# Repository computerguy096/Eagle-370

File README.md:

# Eagle-370
A clone of the original Powerleap PL-iP3/T adapter done in KiCad.

Keep in mind this is not finished, use it at your own risk.

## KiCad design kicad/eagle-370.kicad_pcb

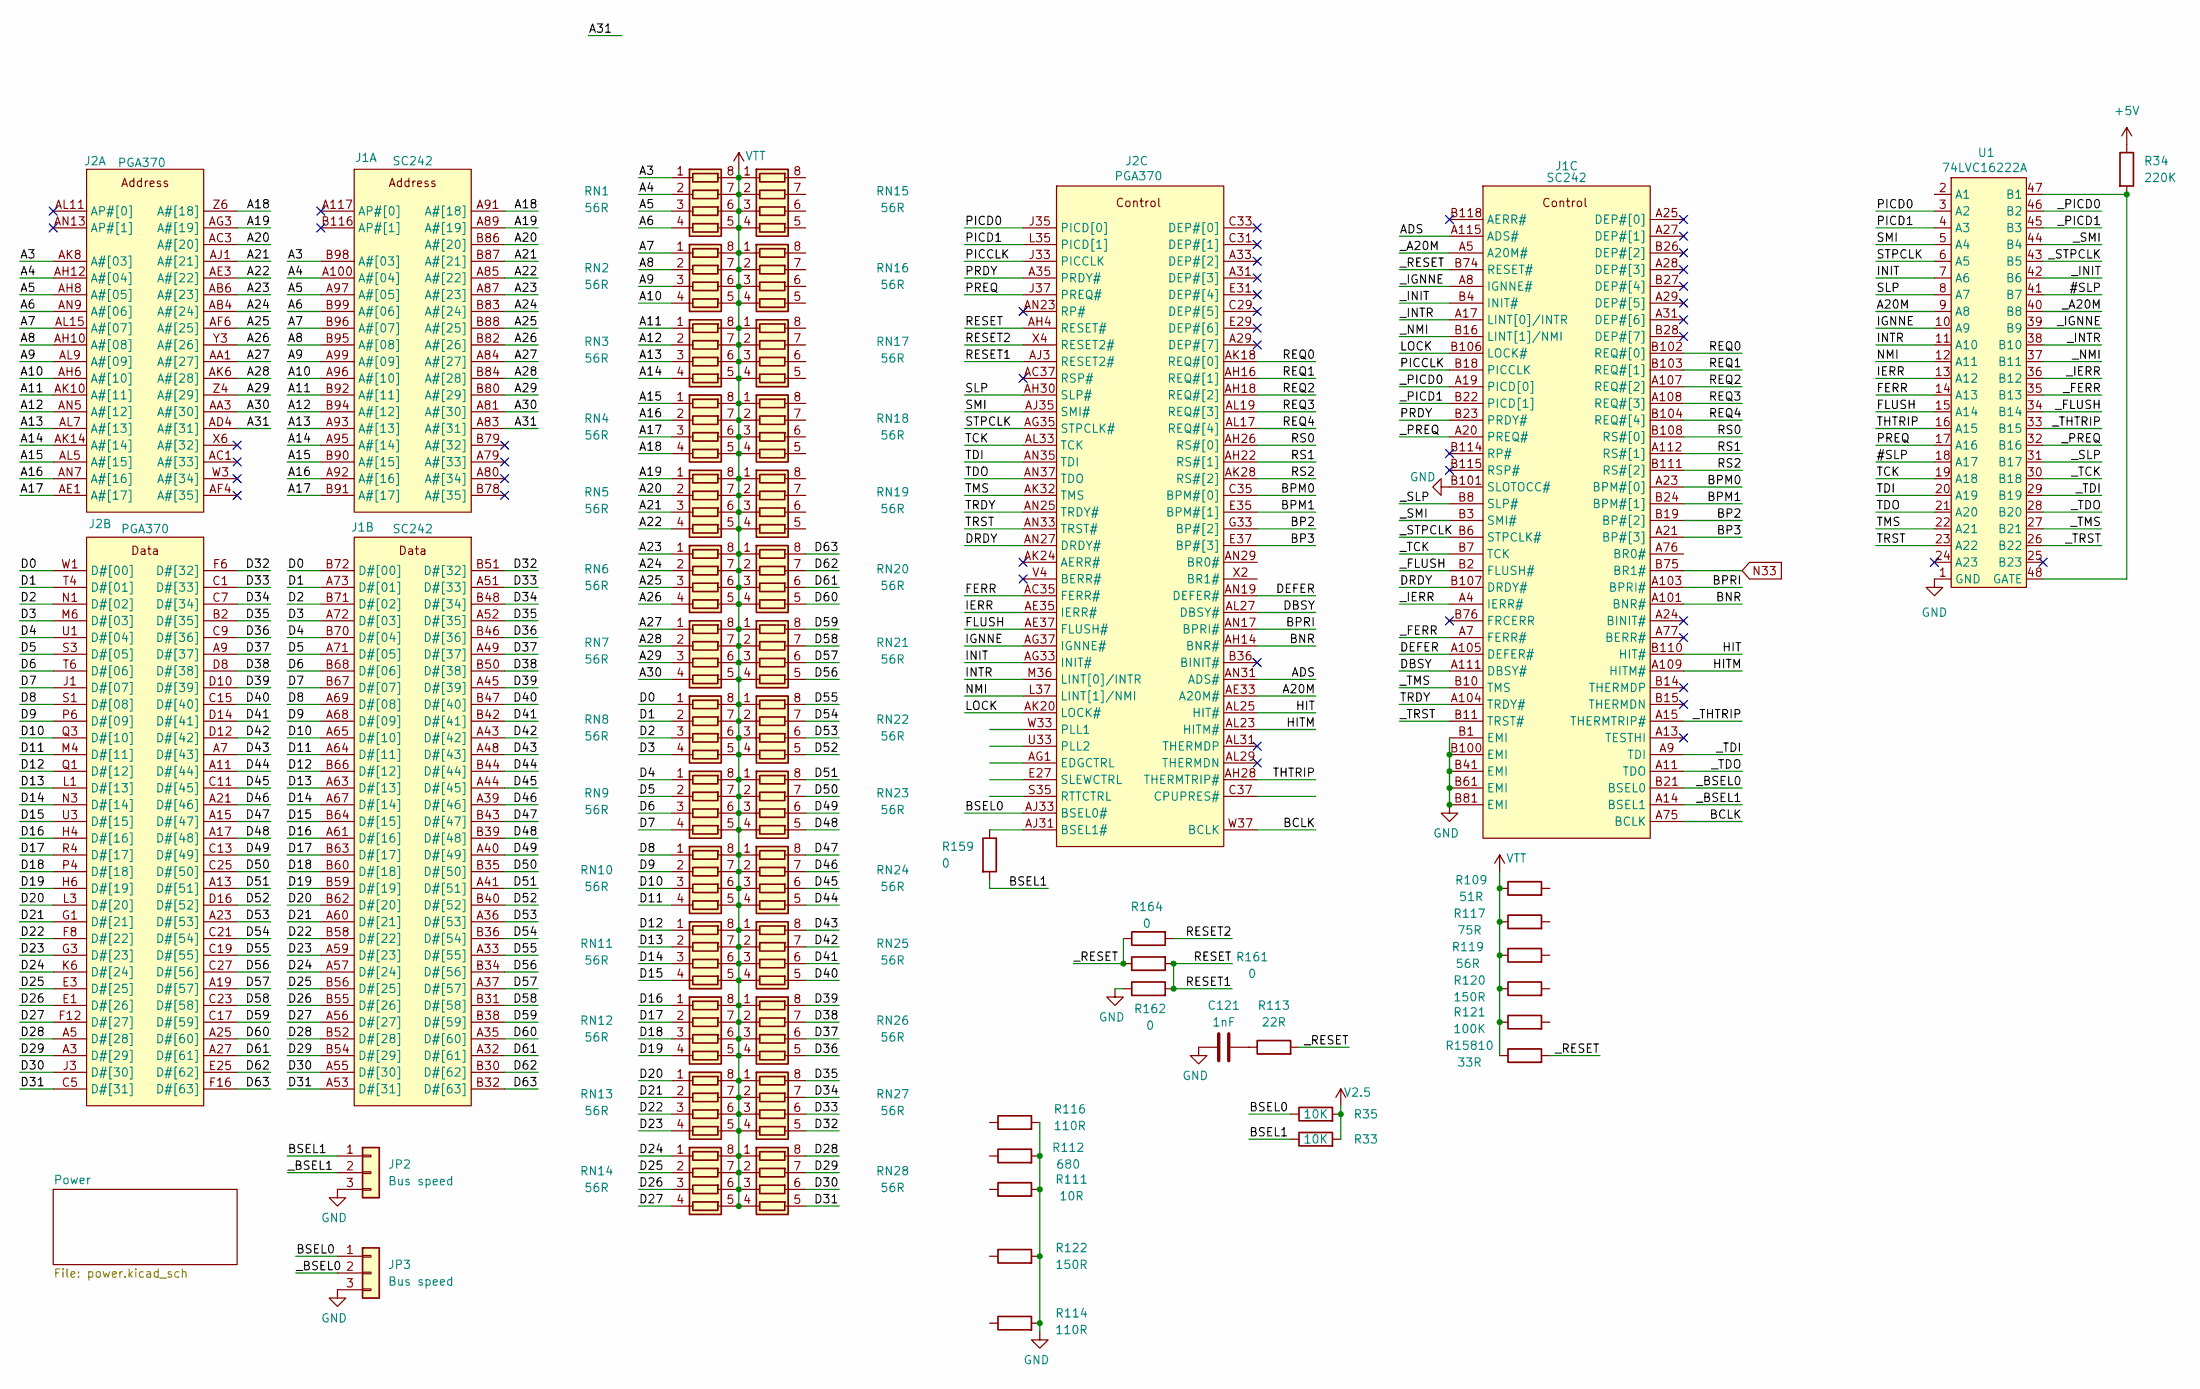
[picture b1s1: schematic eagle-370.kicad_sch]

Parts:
C121: 1nF; C_0805_2012Metric_Pad1.18x1.45mm_HandSolder
J1: SC242; Slot 1
J2: PGA370
JP2, JP3: Bus speed
R33, R35: 10K; R_0805_2012Metric_Pad1.20x1.40mm_HandSolder
R34: 220K; R_0805_2012Metric_Pad1.20x1.40mm_HandSolder
R109: 51R; R_0805_2012Metric_Pad1.20x1.40mm_HandSolder
R111: 10R; R_0805_2012Metric_Pad1.20x1.40mm_HandSolder
R112: 680; R_0805_2012Metric_Pad1.20x1.40mm_HandSolder
R113: 22R; R_0805_2012Metric_Pad1.20x1.40mm_HandSolder
R114, R116: 110R; R_0805_2012Metric_Pad1.20x1.40mm_HandSolder
R117: 75R; R_0805_2012Metric_Pad1.20x1.40mm_HandSolder
R119: 56R; R_0805_2012Metric_Pad1.20x1.40mm_HandSolder
R120, R122: 150R; R_0805_2012Metric_Pad1.20x1.40mm_HandSolder
R121: 100K; R_0805_2012Metric_Pad1.20x1.40mm_HandSolder
R159, R161, R162, R164: 0; R_0805_2012Metric_Pad1.20x1.40mm_HandSolder
R15810: 33R; R_0805_2012Metric_Pad1.20x1.40mm_HandSolder
RN1, RN2, RN3, RN4, RN5, RN6, RN7, RN8, RN9, RN10, RN11, RN12, RN13, RN14, RN15, RN16, RN17, RN18, RN19, RN20, RN21, RN22, RN23, RN24, RN25, RN26, RN27, RN28: 56R; R_Array_Convex_4x0612
U1: 74LVC16222A; SSOP-48_7.5x15.9mm_P0.635mm long pads

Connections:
+5V: R34.1
/#SLP: U1.18 (A17), U1.41 (B7)
/A3: J1.B98 (A#[03]), J2.AK8 (A#[03]), RN1.1 (R1.1)
/A4: J1.A100 (A#[04]), J2.AH12 (A#[04]), RN1.2 (R2.1)
/A5: J1.A97 (A#[05]), J2.AH8 (A#[05]), RN1.3 (R3.1)
/A6: J1.B99 (A#[06]), J2.AN9 (A#[06]), RN1.4 (R4.1)
/A7: J1.B96 (A#[07]), J2.AL15 (A#[07]), RN2.1 (R1.1)
/A8: J1.B95 (A#[08]), J2.AH10 (A#[08]), RN2.2 (R2.1)
/A9: J1.A99 (A#[09]), J2.AL9 (A#[09]), RN2.3 (R3.1)
/A10: J1.A96 (A#[10]), J2.AH6 (A#[10]), RN2.4 (R4.1)
/A11: J1.B92 (A#[11]), J2.AK10 (A#[11]), RN3.1 (R1.1)
/A12: J1.B94 (A#[12]), J2.AN5 (A#[12]), RN3.2 (R2.1)
/A13: J1.A93 (A#[13]), J2.AL7 (A#[13]), RN3.3 (R3.1)
/A14: J1.A95 (A#[14]), J2.AK14 (A#[14]), RN3.4 (R4.1)
/A15: J1.B90 (A#[15]), J2.AL5 (A#[15]), RN4.1 (R1.1)
/A16: J1.A92 (A#[16]), J2.AN7 (A#[16]), RN4.2 (R2.1)
/A17: J1.B91 (A#[17]), J2.AE1 (A#[17]), RN4.3 (R3.1)
/A18: J1.A91 (A#[18]), J2.Z6 (A#[18]), RN4.4 (R4.1)
/A19: J1.A89 (A#[19]), J2.AG3 (A#[19]), RN5.1 (R1.1)
/A20: J1.B86 (A#[20]), J2.AC3 (A#[20]), RN5.2 (R2.1)
/A20M: J2.AE33 (A20M#), U1.9 (A8)
/A21: J1.B87 (A#[21]), J2.AJ1 (A#[21]), RN5.3 (R3.1)
/A22: J1.A85 (A#[22]), J2.AE3 (A#[22]), RN5.4 (R4.1)
/A23: J1.A87 (A#[23]), J2.AB6 (A#[23]), RN6.1 (R1.1)
/A24: J1.B83 (A#[24]), J2.AB4 (A#[24]), RN6.2 (R2.1)
/A25: J1.B88 (A#[25]), J2.AF6 (A#[25]), RN6.3 (R3.1)
/A26: J1.B82 (A#[26]), J2.Y3 (A#[26]), RN6.4 (R4.1)
/A27: J1.A84 (A#[27]), J2.AA1 (A#[27]), RN7.1 (R1.1)
/A28: J1.B84 (A#[28]), J2.AK6 (A#[28]), RN7.2 (R2.1)
/A29: J1.B80 (A#[29]), J2.Z4 (A#[29]), RN7.3 (R3.1)
/A30: J1.A81 (A#[30]), J2.AA3 (A#[30]), RN7.4 (R4.1)
/A31: J1.A83 (A#[31]), J2.AD4 (A#[31])
/ADS: J1.A115 (ADS#), J2.AN31 (ADS#)
/BCLK: J1.A75 (BCLK), J2.W37 (BCLK)
/BNR: J1.A101 (BNR#), J2.AH14 (BNR#)
/BP2: J1.B19 (BP#[2]), J2.G33 (BP#[2])
/BP3: J1.A21 (BP#[3]), J2.E37 (BP#[3])
/BPM0: J1.A23 (BPM#[0]), J2.C35 (BPM#[0])
/BPM1: J1.B24 (BPM#[1]), J2.E35 (BPM#[1])
/BPRI: J1.A103 (BPRI#), J2.AN17 (BPRI#)
/BSEL0: J2.AJ33 (BSEL0#), JP3.1, R35.1
/BSEL1: JP2.1, R33.1, R159.2
/D0: J1.B72 (D#[00]), J2.W1 (D#[00]), RN8.1 (R1.1)
/D1: J1.A73 (D#[01]), J2.T4 (D#[01]), RN8.2 (R2.1)
/D2: J1.B71 (D#[02]), J2.N1 (D#[02]), RN8.3 (R3.1)
/D3: J1.A72 (D#[03]), J2.M6 (D#[03]), RN8.4 (R4.1)
/D4: J1.B70 (D#[04]), J2.U1 (D#[04]), RN9.1 (R1.1)
/D5: J1.A71 (D#[05]), J2.S3 (D#[05]), RN9.2 (R2.1)
/D6: J1.B68 (D#[06]), J2.T6 (D#[06]), RN9.3 (R3.1)
/D7: J1.B67 (D#[07]), J2.J1 (D#[07]), RN9.4 (R4.1)
/D8: J1.A69 (D#[08]), J2.S1 (D#[08]), RN10.1 (R1.1)
/D9: J1.A68 (D#[09]), J2.P6 (D#[09]), RN10.2 (R2.1)
/D10: J1.A65 (D#[10]), J2.Q3 (D#[10]), RN10.3 (R3.1)
/D11: J1.A64 (D#[11]), J2.M4 (D#[11]), RN10.4 (R4.1)
/D12: J1.B66 (D#[12]), J2.Q1 (D#[12]), RN11.1 (R1.1)
/D13: J1.A63 (D#[13]), J2.L1 (D#[13]), RN11.2 (R2.1)
/D14: J1.A67 (D#[14]), J2.N3 (D#[14]), RN11.3 (R3.1)
/D15: J1.B64 (D#[15]), J2.U3 (D#[15]), RN11.4 (R4.1)
/D16: J1.A61 (D#[16]), J2.H4 (D#[16]), RN12.1 (R1.1)
/D17: J1.B63 (D#[17]), J2.R4 (D#[17]), RN12.2 (R2.1)
/D18: J1.B60 (D#[18]), J2.P4 (D#[18]), RN12.3 (R3.1)
/D19: J1.B59 (D#[19]), J2.H6 (D#[19]), RN12.4 (R4.1)
/D20: J1.B62 (D#[20]), J2.L3 (D#[20]), RN13.1 (R1.1)
/D21: J1.A60 (D#[21]), J2.G1 (D#[21]), RN13.2 (R2.1)
/D22: J1.B58 (D#[22]), J2.F8 (D#[22]), RN13.3 (R3.1)
/D23: J1.A59 (D#[23]), J2.G3 (D#[23]), RN13.4 (R4.1)
/D24: J1.A57 (D#[24]), J2.K6 (D#[24]), RN14.1 (R1.1)
/D25: J1.B56 (D#[25]), J2.E3 (D#[25]), RN14.2 (R2.1)
/D26: J1.B55 (D#[26]), J2.E1 (D#[26]), RN14.3 (R3.1)
/D27: J1.A56 (D#[27]), J2.F12 (D#[27]), RN14.4 (R4.1)
/D28: J1.B52 (D#[28]), J2.A5 (D#[28]), RN28.8 (R1.2)
/D29: J1.B54 (D#[29]), J2.A3 (D#[29]), RN28.7 (R2.2)
/D30: J1.A55 (D#[30]), J2.J3 (D#[30]), RN28.6 (R3.2)
/D31: J1.A53 (D#[31]), J2.C5 (D#[31]), RN28.5 (R4.2)
/D32: J1.B51 (D#[32]), J2.F6 (D#[32]), RN27.5 (R4.2)
/D33: J1.A51 (D#[33]), J2.C1 (D#[33]), RN27.6 (R3.2)
/D34: J1.B48 (D#[34]), J2.C7 (D#[34]), RN27.7 (R2.2)
/D35: J1.A52 (D#[35]), J2.B2 (D#[35]), RN27.8 (R1.2)
/D36: J1.B46 (D#[36]), J2.C9 (D#[36]), RN26.5 (R4.2)
/D37: J1.A49 (D#[37]), J2.A9 (D#[37]), RN26.6 (R3.2)
/D38: J1.B50 (D#[38]), J2.D8 (D#[38]), RN26.7 (R2.2)
/D39: J1.A45 (D#[39]), J2.D10 (D#[39]), RN26.8 (R1.2)
/D40: J1.B47 (D#[40]), J2.C15 (D#[40]), RN25.5 (R4.2)
/D41: J1.B42 (D#[41]), J2.D14 (D#[41]), RN25.6 (R3.2)
/D42: J1.A43 (D#[42]), J2.D12 (D#[42]), RN25.7 (R2.2)
/D43: J1.A48 (D#[43]), J2.A7 (D#[43]), RN25.8 (R1.2)
/D44: J1.B44 (D#[44]), J2.A11 (D#[44]), RN24.5 (R4.2)
/D45: J1.A44 (D#[45]), J2.C11 (D#[45]), RN24.6 (R3.2)
/D46: J1.A39 (D#[46]), J2.A21 (D#[46]), RN24.7 (R2.2)
/D47: J1.B43 (D#[47]), J2.A15 (D#[47]), RN24.8 (R1.2)
/D48: J1.B39 (D#[48]), J2.A17 (D#[48]), RN23.5 (R4.2)
/D49: J1.A40 (D#[49]), J2.C13 (D#[49]), RN23.6 (R3.2)
/D50: J1.B35 (D#[50]), J2.C25 (D#[50]), RN23.7 (R2.2)
/D51: J1.A41 (D#[51]), J2.A13 (D#[51]), RN23.8 (R1.2)
/D52: J1.B40 (D#[52]), J2.D16 (D#[52]), RN22.5 (R4.2)
/D53: J1.A36 (D#[53]), J2.A23 (D#[53]), RN22.6 (R3.2)
/D54: J1.B36 (D#[54]), J2.C21 (D#[54]), RN22.7 (R2.2)
/D55: J1.A33 (D#[55]), J2.C19 (D#[55]), RN22.8 (R1.2)
/D56: J1.B34 (D#[56]), J2.C27 (D#[56]), RN21.5 (R4.2)
/D57: J1.A37 (D#[57]), J2.A19 (D#[57]), RN21.6 (R3.2)
/D58: J1.B31 (D#[58]), J2.C23 (D#[58]), RN21.7 (R2.2)
/D59: J1.B38 (D#[59]), J2.C17 (D#[59]), RN21.8 (R1.2)
/D60: J1.A35 (D#[60]), J2.A25 (D#[60]), RN20.5 (R4.2)
/D61: J1.A32 (D#[61]), J2.A27 (D#[61]), RN20.6 (R3.2)
/D62: J1.B30 (D#[62]), J2.E25 (D#[62]), RN20.7 (R2.2)
/D63: J1.B32 (D#[63]), J2.F16 (D#[63]), RN20.8 (R1.2)
/DBSY: J1.A111 (DBSY#), J2.AL27 (DBSY#)
/DEFER: J1.A105 (DEFER#), J2.AN19 (DEFER#)
/DRDY: J1.B107 (DRDY#), J2.AN27 (DRDY#)
/FERR: J2.AC35 (FERR#), U1.14 (A13)
/FLUSH: J2.AE37 (FLUSH#), U1.15 (A14)
/HIT: J1.B110 (HIT#), J2.AL25 (HIT#)
/HITM: J1.A109 (HITM#), J2.AL23 (HITM#)
/IERR: J2.AE35 (IERR#), U1.13 (A12)
/IGNNE: J2.AG37 (IGNNE#), U1.10 (A9)
/INIT: J2.AG33 (INIT#), U1.7 (A6)
/INTR: J2.M36 (LINT[0]/INTR), U1.11 (A10)
/LOCK: J1.B106 (LOCK#), J2.AK20 (LOCK#)
/NMI: J2.L37 (LINT[1]/NMI), U1.12 (A11)
/PICCLK: J1.B18 (PICCLK), J2.J33 (PICCLK)
/PICD0: J2.J35 (PICD[0]), U1.3 (A2)
/PICD1: J2.L35 (PICD[1]), U1.4 (A3)
/PRDY: J1.B23 (PRDY#), J2.A35 (PRDY#)
/PREQ: J2.J37 (PREQ#), U1.17 (A16)
/REQ0: J1.B102 (REQ#[0]), J2.AK18 (REQ#[0])
/REQ1: J1.B103 (REQ#[1]), J2.AH16 (REQ#[1])
/REQ2: J1.A107 (REQ#[2]), J2.AH18 (REQ#[2])
/REQ3: J1.A108 (REQ#[3]), J2.AL19 (REQ#[3])
/REQ4: J1.B104 (REQ#[4]), J2.AL17 (REQ#[4])
/RESET: J2.AH4 (RESET#), J2.AJ3 (RESET2#), R161.2, R162.2
/RESET2: J2.X4 (RESET2#), R164.2
/RS0: J1.B108 (RS#[0]), J2.AH26 (RS#[0])
/RS1: J1.A112 (RS#[1]), J2.AH22 (RS#[1])
/RS2: J1.B111 (RS#[2]), J2.AK28 (RS#[2])
/SLP: J2.AH30 (SLP#), U1.8 (A7)
/SMI: J2.AJ35 (SMI#), U1.5 (A4)
/STPCLK: J2.AG35 (STPCLK#), U1.6 (A5)
/TCK: J2.AL33 (TCK), U1.19 (A18)
/TDI: J2.AN35 (TDI), U1.20 (A19)
/TDO: J2.AN37 (TDO), U1.21 (A20)
/THTRIP: J2.AH28 (THERMTRIP#), U1.16 (A15)
/TMS: J2.AK32 (TMS), U1.22 (A21)
/TRDY: J1.A104 (TRDY#), J2.AN25 (TRDY#)
/TRST: J2.AN33 (TRST#), U1.23 (A22)
/_A20M: J1.A5 (A20M#), U1.40 (B8)
/_BSEL0: J1.B21 (BSEL0), JP3.2
/_FERR: J1.A7 (FERR#), U1.35 (B13)
/_FLUSH: J1.B2 (FLUSH#), U1.34 (B14)
/_IERR: J1.A4 (IERR#), U1.36 (B12)
/_IGNNE: J1.A8 (IGNNE#), U1.39 (B9)
/_INIT: J1.B4 (INIT#), U1.42 (B6)
/_INTR: J1.A17 (LINT[0]/INTR), U1.38 (B10)
/_NMI: J1.B16 (LINT[1]/NMI), U1.37 (B11)
/_PICD0: J1.A19 (PICD[0]), U1.46 (B2)
/_PICD1: J1.B22 (PICD[1]), U1.45 (B3)
/_PREQ: J1.A20 (PREQ#), U1.32 (B16)
/_RESET: J1.B74 (RESET#), R113.2, R161.1, R164.1, R15810.2
/_SLP: J1.B8 (SLP#), U1.31 (B17)
/_SMI: J1.B3 (SMI#), U1.44 (B4)
/_STPCLK: J1.B6 (STPCLK#), U1.43 (B5)
/_TCK: J1.B7 (TCK), U1.30 (B18)
/_TDI: J1.A9 (TDI), U1.29 (B19)
/_TDO: J1.A11 (TDO), U1.28 (B20)
/_THTRIP: J1.A15 (THERMTRIP#), U1.33 (B15)
/_TMS: J1.B10 (TMS), U1.27 (B21)
/_TRST: J1.B11 (TRST#), U1.26 (B22)
N33: J1.B75 (BR1#)
unnamed: C121.2, R113.1
unnamed: J2.AJ31 (BSEL1#), R159.1
unnamed: R34.2, U1.47 (B1), U1.48 (GATE)
V2.5: R33.2, R35.2; also elsewhere on the board
VTT: R109.1, R117.1, R119.1, R120.1, R121.1, R15810.1, RN1.5 (R4.2), RN1.6 (R3.2), RN1.7 (R2.2), RN1.8 (R1.2), RN2.5 (R4.2), RN2.6 (R3.2), RN2.7 (R2.2), RN2.8 (R1.2), RN3.5 (R4.2), RN3.6 (R3.2), RN3.7 (R2.2), RN3.8 (R1.2), RN4.5 (R4.2), RN4.6 (R3.2), RN4.7 (R2.2), RN4.8 (R1.2), RN5.5 (R4.2), RN5.6 (R3.2), RN5.7 (R2.2), RN5.8 (R1.2), RN6.5 (R4.2), RN6.6 (R3.2), RN6.7 (R2.2), RN6.8 (R1.2), RN7.5 (R4.2), RN7.6 (R3.2), RN7.7 (R2.2), RN7.8 (R1.2), RN8.5 (R4.2), RN8.6 (R3.2), RN8.7 (R2.2), RN8.8 (R1.2), RN9.5 (R4.2), RN9.6 (R3.2), RN9.7 (R2.2), RN9.8 (R1.2), RN10.5 (R4.2), RN10.6 (R3.2), RN10.7 (R2.2), RN10.8 (R1.2), RN11.5 (R4.2), RN11.6 (R3.2), RN11.7 (R2.2), RN11.8 (R1.2), RN12.5 (R4.2), RN12.6 (R3.2), RN12.7 (R2.2), RN12.8 (R1.2), RN13.5 (R4.2), RN13.6 (R3.2), RN13.7 (R2.2), RN13.8 (R1.2), RN14.5 (R4.2), RN14.6 (R3.2), RN14.7 (R2.2), RN14.8 (R1.2), RN15.1 (R1.1), RN15.2 (R2.1), RN15.3 (R3.1), RN15.4 (R4.1), RN16.1 (R1.1), RN16.2 (R2.1), RN16.3 (R3.1), RN16.4 (R4.1), RN17.1 (R1.1), RN17.2 (R2.1), RN17.3 (R3.1), RN17.4 (R4.1), RN18.1 (R1.1), RN18.2 (R2.1), RN18.3 (R3.1), RN18.4 (R4.1), RN19.1 (R1.1), RN19.2 (R2.1), RN19.3 (R3.1), RN19.4 (R4.1), RN20.1 (R1.1), RN20.2 (R2.1), RN20.3 (R3.1), RN20.4 (R4.1), RN21.1 (R1.1), RN21.2 (R2.1), RN21.3 (R3.1), RN21.4 (R4.1), RN22.1 (R1.1), RN22.2 (R2.1), RN22.3 (R3.1), RN22.4 (R4.1), RN23.1 (R1.1), RN23.2 (R2.1), RN23.3 (R3.1), RN23.4 (R4.1), RN24.1 (R1.1), RN24.2 (R2.1), RN24.3 (R3.1), RN24.4 (R4.1), RN25.1 (R1.1), RN25.2 (R2.1), RN25.3 (R3.1), RN25.4 (R4.1), RN26.1 (R1.1), RN26.2 (R2.1), RN26.3 (R3.1), RN26.4 (R4.1), RN27.1 (R1.1), RN27.2 (R2.1), RN27.3 (R3.1), RN27.4 (R4.1), RN28.1 (R1.1), RN28.2 (R2.1), RN28.3 (R3.1), RN28.4 (R4.1); also elsewhere on the board

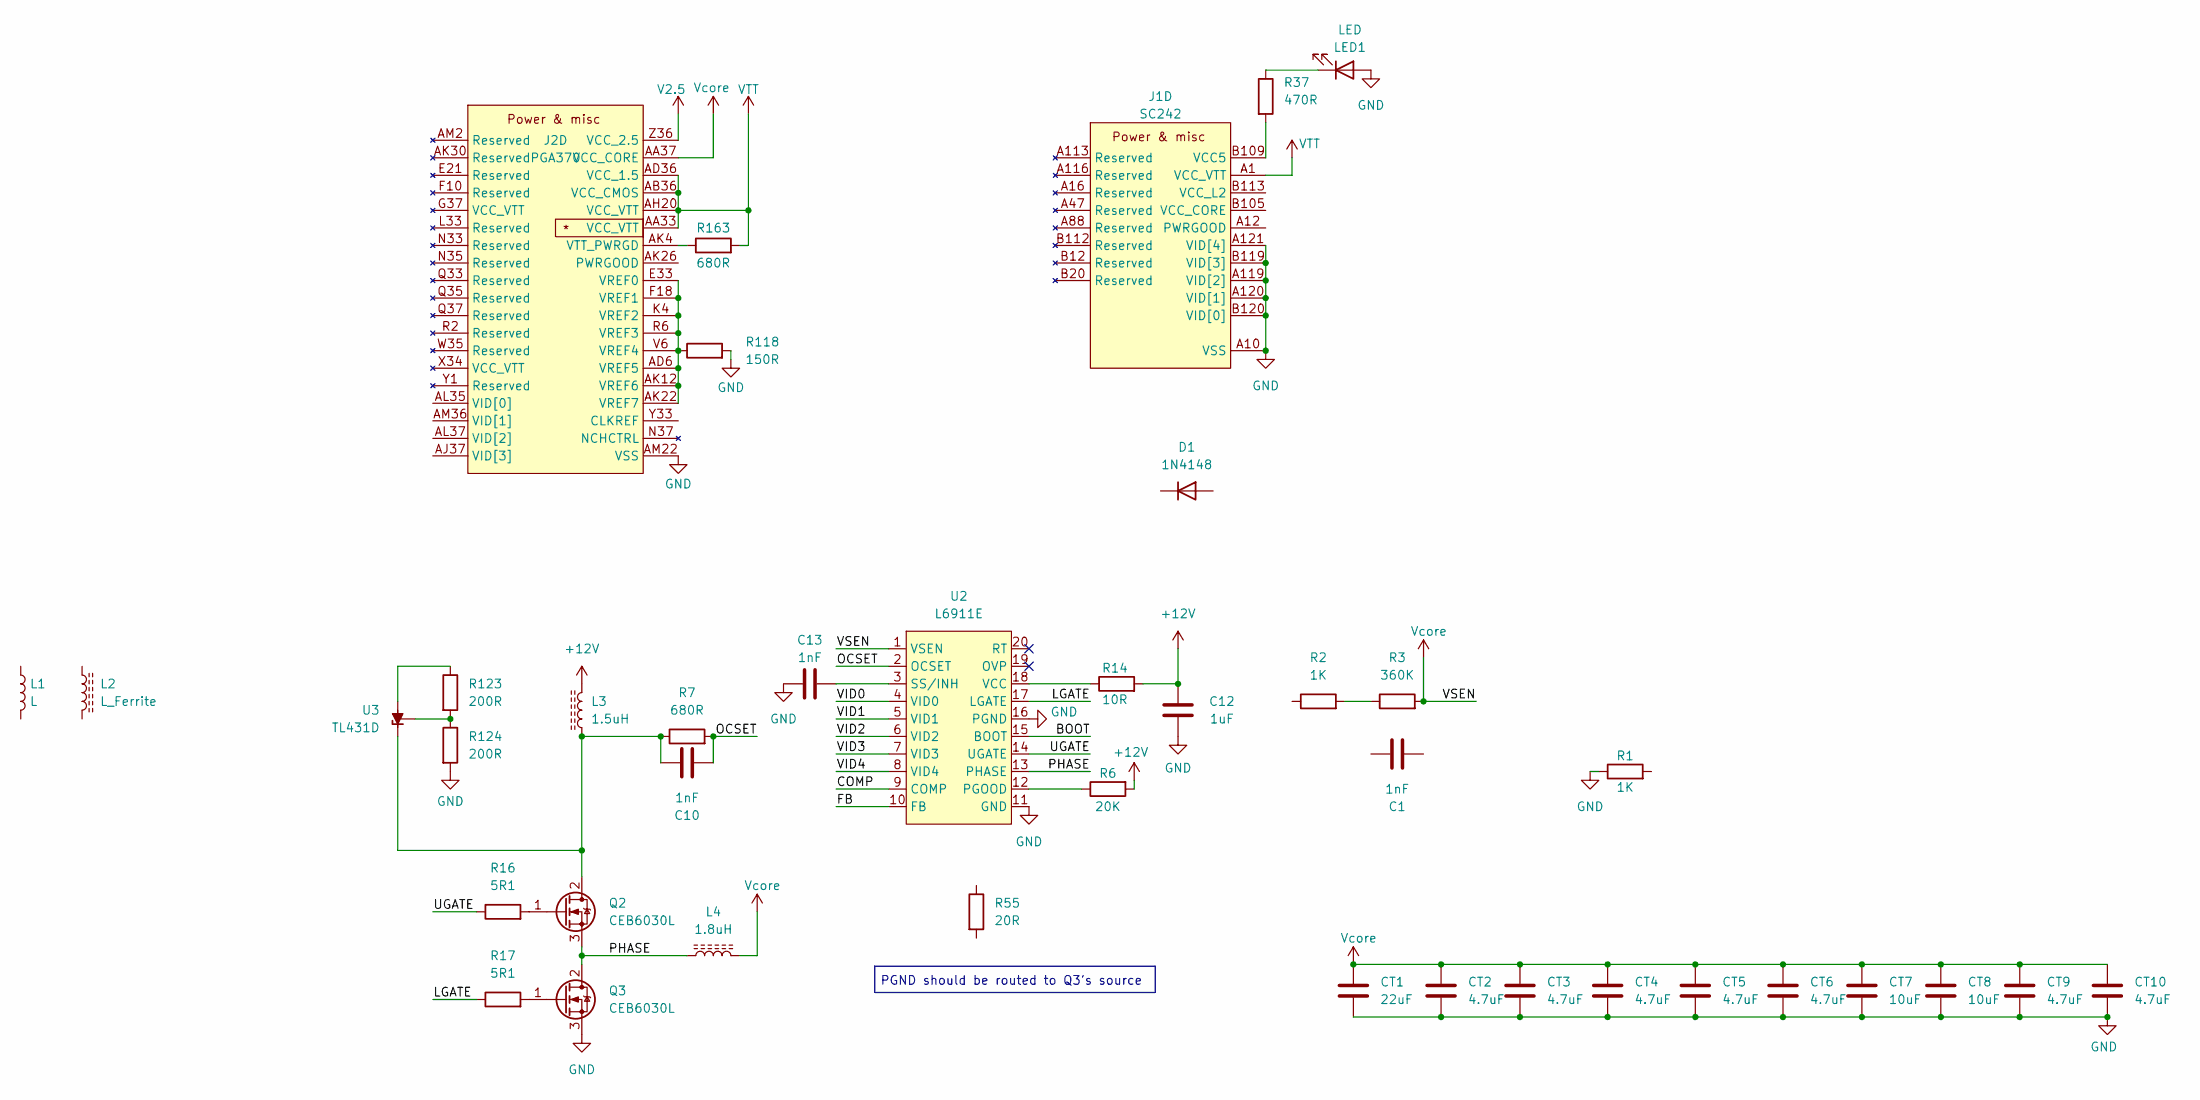
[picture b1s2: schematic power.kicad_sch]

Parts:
C1, C10, C13: 1nF; C_0805_2012Metric_Pad1.18x1.45mm_HandSolder
C12: 1uF; C_0805_2012Metric_Pad1.18x1.45mm_HandSolder
CT1: 22uF; C_1206_3216Metric_Pad1.33x1.80mm_HandSolder
CT2, CT3, CT4, CT5, CT6, CT9, CT10: 4.7uF; C_1206_3216Metric_Pad1.33x1.80mm_HandSolder
CT7, CT8: 10uF; C_1206_3216Metric_Pad1.33x1.80mm_HandSolder
D1: 1N4148; SOT-23
J1: SC242; Slot 1
J2: PGA370
L1: L; L_0805_2012Metric_Pad1.05x1.20mm_HandSolder
L2: L_Ferrite; L_Toroid_Vertical_L16.8mm_W9.2mm_P7.10mm_Vishay_TJ3_BigPads
L3: 1.5uH; L_Toroid_Vertical_L10.0mm_W5.0mm_P5.08mm
L4: 1.8uH; L_Toroid_Vertical_L16.8mm_W9.2mm_P7.10mm_Vishay_TJ3_BigPads
LED1: LED
Q2, Q3: CEB6030L; TO-252-2
R1, R2: 1K; R_0805_2012Metric_Pad1.20x1.40mm_HandSolder
R3: 360K; R_0805_2012Metric_Pad1.20x1.40mm_HandSolder
R6: 20K; R_0805_2012Metric_Pad1.20x1.40mm_HandSolder
R7, R163: 680R; R_0805_2012Metric_Pad1.20x1.40mm_HandSolder
R14: 10R; R_0805_2012Metric_Pad1.20x1.40mm_HandSolder
R16, R17: 5R1; R_0805_2012Metric_Pad1.20x1.40mm_HandSolder
R37: 470R; R_0805_2012Metric_Pad1.20x1.40mm_HandSolder
R55: 20R; R_0805_2012Metric_Pad1.20x1.40mm_HandSolder
R118: 150R; R_0805_2012Metric_Pad1.20x1.40mm_HandSolder
R123, R124: 200R; R_0805_2012Metric_Pad1.20x1.40mm_HandSolder
U2: L6911E; SOP-20_7.5x12.8mm_P1.27mm
U3: TL431D; SOT-223-3_TabPin2

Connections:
+12V: C12.2, L3.2, R6.2, R14.2
/Power/BOOT: U2.15 (BOOT)
/Power/COMP: U2.9 (COMP)
/Power/FB: U2.10 (FB)
/Power/LGATE: R17.1, U2.17 (LGATE)
/Power/OCSET: C10.2, R7.2, U2.2 (OCSET)
/Power/PHASE: L4.1, Q2.3 (S), Q3.2 (D), U2.13 (PHASE)
/Power/UGATE: R16.1, U2.14 (UGATE)
/Power/VID0: U2.4 (VID0)
/Power/VID1: U2.5 (VID1)
/Power/VID2: U2.6 (VID2)
/Power/VID3: U2.7 (VID3)
/Power/VID4: U2.8 (VID4)
unnamed: J1.B109 (VCC5), R37.2
unnamed: J2.AD6 (VREF5), J2.AK12 (VREF6), J2.AK22 (VREF7), J2.E33 (VREF0), J2.F18 (VREF1), J2.K4 (VREF2), J2.R6 (VREF3), J2.V6 (VREF4), R118.1
unnamed: J2.AK4 (VTT_PWRGD), R163.1
unnamed: LED1.1 (K), R37.1
unnamed: C10.1, L3.1, Q2.2 (D), R7.1, U3.1 (K)
unnamed: Q2.1 (G), R16.2
unnamed: Q3.1 (G), R17.2
unnamed: R2.2, R3.1
unnamed: R6.1, U2.12 (PGOOD)
unnamed: C13.2, U2.3 (SS/INH)
unnamed: R14.1, U2.18 (VCC)
unnamed: R123.1, U3.3 (A)
unnamed: R123.2, R124.1, U3.2 (REF)
V2.5: J2.Z36 (VCC_2.5); also elsewhere on the board
VCC_CORE: J1.B13 (VCC_CORE), J1.B17 (VCC_CORE), J1.B25 (VCC_CORE), J1.B29 (VCC_CORE), J1.B33 (VCC_CORE), J1.B37 (VCC_CORE), J1.B45 (VCC_CORE), J1.B49 (VCC_CORE), J1.B53 (VCC_CORE), J1.B57 (VCC_CORE), J1.B65 (VCC_CORE), J1.B69 (VCC_CORE), J1.B73 (VCC_CORE), J1.B77 (VCC_CORE), J1.B85 (VCC_CORE), J1.B89 (VCC_CORE), J1.B93 (VCC_CORE), J1.B97 (VCC_CORE), J1.B105 (VCC_CORE)
VCC_L2: J1.B113 (VCC_L2), J1.B117 (VCC_L2), J1.B121 (VCC_L2)
VTT: J1.A1 (VCC_VTT), J1.A3 (VCC_VTT), J1.B5 (VCC_VTT), J1.B9 (VCC_VTT), J2.AA33 (VCC_VTT), J2.AA35 (VCC_VTT), J2.AB36 (VCC_CMOS), J2.AD36 (VCC_1.5), J2.AH20 (VCC_VTT), J2.AK16 (VCC_VTT), J2.AL13 (VCC_VTT), J2.AL21 (VCC_VTT), J2.AN11 (VCC_VTT), J2.AN15 (VCC_VTT), J2.AN21 (VCC_VTT), J2.E23 (VCC_VTT), J2.G35 (VCC_VTT), J2.S33 (VCC_VTT), J2.S37 (VCC_VTT), J2.U35 (VCC_VTT), J2.U37 (VCC_VTT), R163.2; also elsewhere on the board
Vcore: CT1.1, CT2.1, CT3.1, CT4.1, CT5.1, CT6.1, CT7.1, CT8.1, CT9.1, CT10.1, J2.AA5 (VCC_CORE), J2.AA37 (VCC_CORE), J2.AB2 (VCC_CORE), J2.AB34 (VCC_CORE), J2.AD32 (VCC_CORE), J2.AE5 (VCC_CORE), J2.AF2 (VCC_CORE), J2.AF34 (VCC_CORE), J2.AH24 (VCC_CORE), J2.AH32 (VCC_CORE), J2.AH36 (VCC_CORE), J2.AJ5 (VCC_CORE), J2.AJ9 (VCC_CORE), J2.AJ13 (VCC_CORE), J2.AJ17 (VCC_CORE), J2.AJ21 (VCC_CORE), J2.AJ25 (VCC_CORE), J2.AJ29 (VCC_CORE), J2.AK2 (VCC_CORE), J2.AK34 (VCC_CORE), J2.AM4 (VCC_CORE), J2.AM8 (VCC_CORE), J2.AM12 (VCC_CORE), J2.AM16 (VCC_CORE), J2.AM20 (VCC_CORE), J2.AM24 (VCC_CORE), J2.AM28 (VCC_CORE), J2.AM32 (VCC_CORE), J2.B6 (VCC_CORE), J2.B10 (VCC_CORE), J2.B14 (VCC_CORE), J2.B18 (VCC_CORE), J2.B22 (VCC_CORE), J2.B26 (VCC_CORE), J2.B30 (VCC_CORE), J2.B34 (VCC_CORE), J2.C3 (VCC_CORE), J2.D6 (VCC_CORE), J2.D20 (VCC_CORE), J2.D24 (VCC_CORE), J2.D28 (VCC_CORE), J2.D32 (VCC_CORE), J2.D36 (VCC_CORE), J2.E5 (VCC_CORE), J2.E9 (VCC_CORE), J2.E13 (VCC_CORE), J2.E17 (VCC_CORE), J2.F2 (VCC_CORE), J2.F4 (VCC_CORE), J2.F14 (VCC_CORE), J2.F22 (VCC_CORE), J2.F26 (VCC_CORE), J2.F30 (VCC_CORE), J2.F34 (VCC_CORE), J2.H32 (VCC_CORE), J2.H36 (VCC_CORE), J2.J5 (VCC_CORE), J2.K2 (VCC_CORE), J2.K32 (VCC_CORE), J2.K34 (VCC_CORE), J2.M32 (VCC_CORE), J2.N5 (VCC_CORE), J2.P2 (VCC_CORE), J2.P34 (VCC_CORE), J2.R32 (VCC_CORE), J2.R36 (VCC_CORE), J2.S5 (VCC_CORE), J2.T2 (VCC_CORE), J2.T34 (VCC_CORE), J2.V32 (VCC_CORE), J2.V36 (VCC_CORE), J2.W5 (VCC_CORE), J2.Y35 (VCC_CORE), J2.Z32 (VCC_CORE), L4.2, R3.2, U2.1 (VSEN)

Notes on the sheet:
PGND should be routed to Q3's source

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
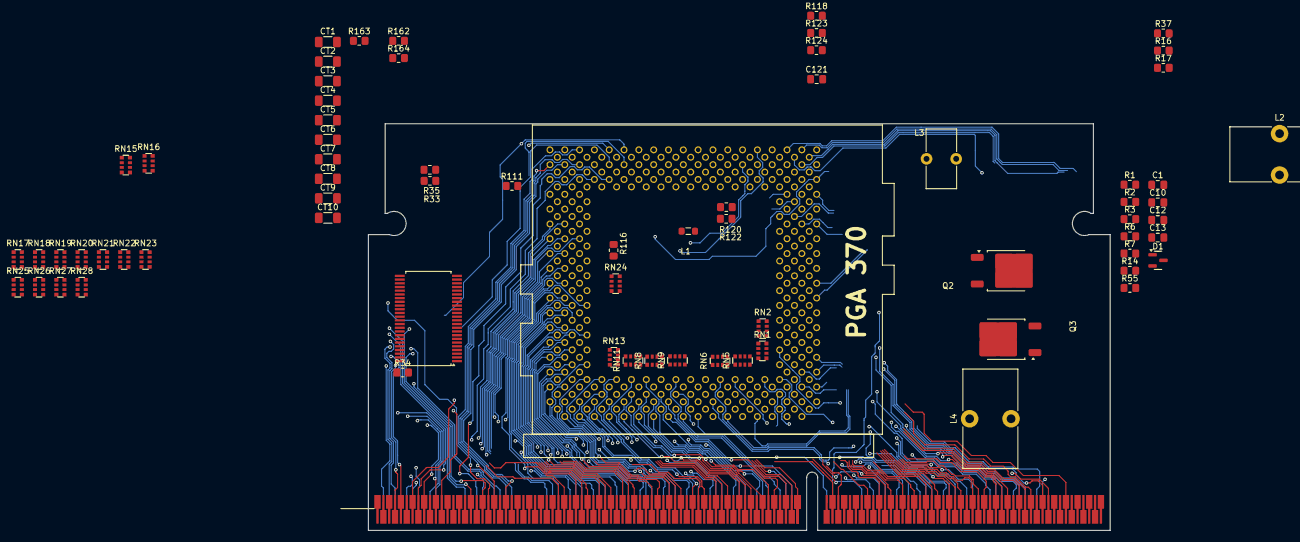
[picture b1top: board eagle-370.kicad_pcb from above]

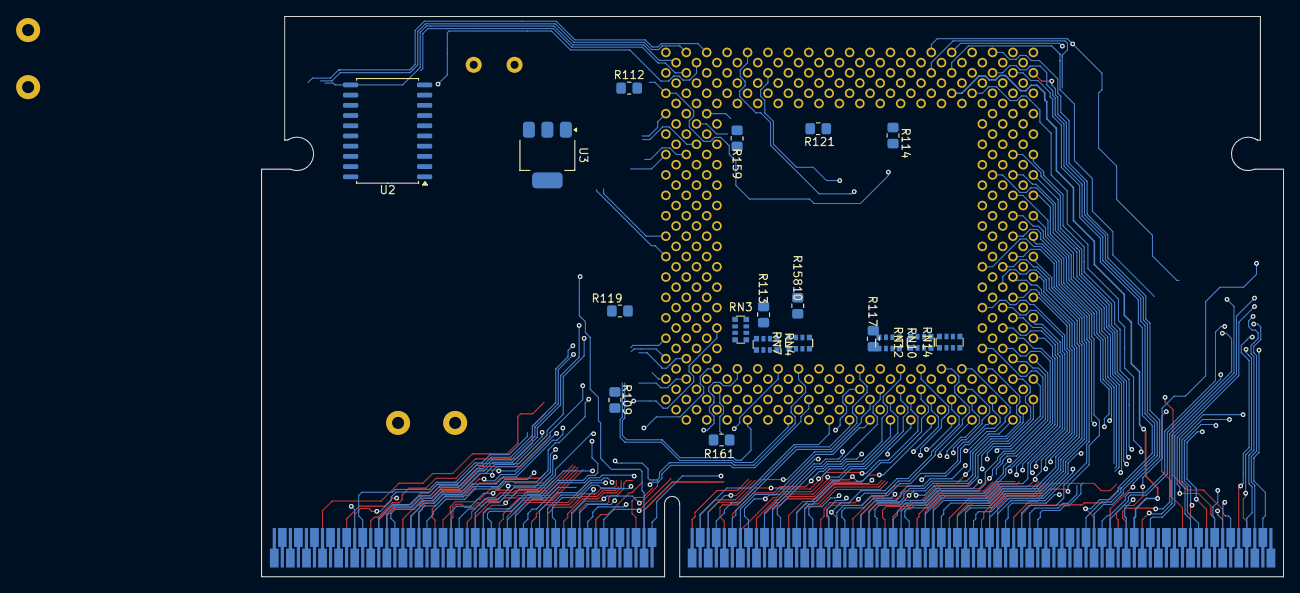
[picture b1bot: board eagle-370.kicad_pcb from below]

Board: 4 copper layers, 127.1 x 69.7 mm, 88 parts (18 on the bottom side), 190 nets.
